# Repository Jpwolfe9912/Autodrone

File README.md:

# F722 Flight Controller V4

[Autodrone.pdf](https://github.com/Jpwolfe9912/Autodrone/files/7485937/Autodrone.pdf)

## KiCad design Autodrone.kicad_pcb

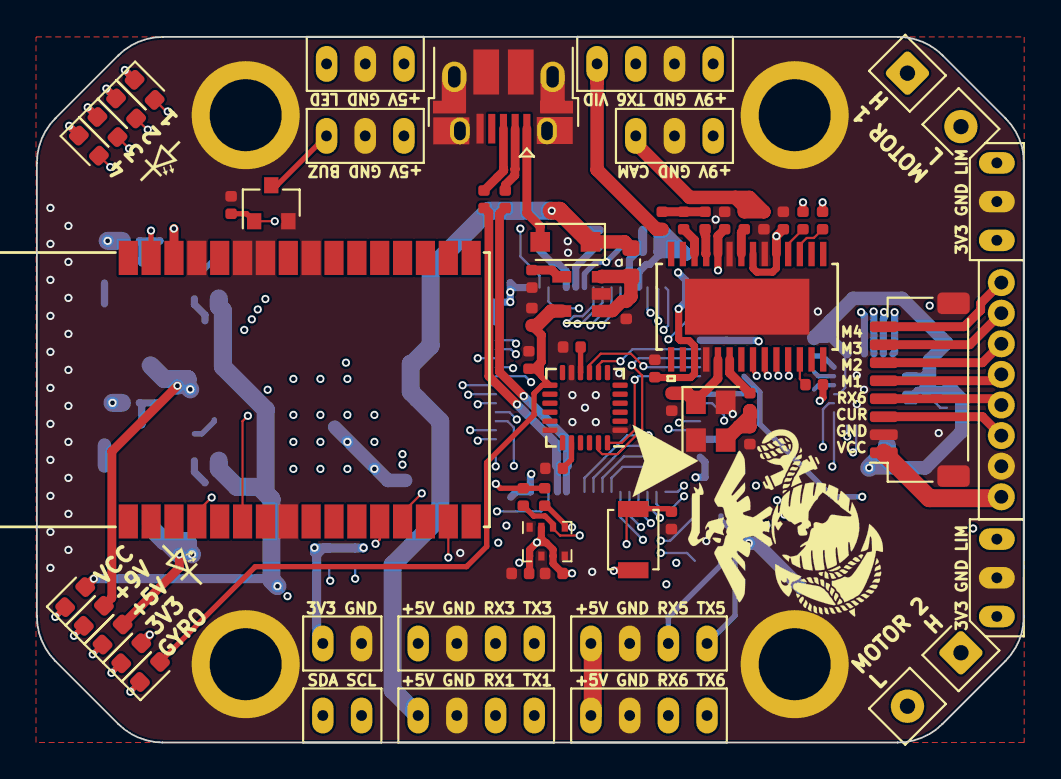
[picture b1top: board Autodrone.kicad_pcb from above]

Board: 6 copper layers, 54.8 x 39.2 mm, 142 parts (0 on the bottom side), 111 nets.

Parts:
C1, C2, C6, C8, C18, C20, C21, C22, C31, C32, C33, C34, C40, C41, C42, C43, C44, C45: 0.1uF; C_0402_1005Metric
C3: 33uF; C_0402_1005Metric
C4: 22uF; C_0402_1005Metric
C5, C7, C39: 4.7uF; C_0402_1005Metric
C9, C10: 330pF; C_0402_1005Metric
C11, C12: 1pF; C_0402_1005Metric
C13, C14, C29, C30: 10uF; C_0402_1005Metric
C15, C37: 1uF; C_0402_1005Metric
C16, C38: 10nF; C_0402_1005Metric
C17, C46: 2.2uF; C_0402_1005Metric
C19: 2.2nF; C_0402_1005Metric
C23, C25: 0.01uF; C_0402_1005Metric
C24: 100uF; CP_EIA-3528-15_AVX-H_Pad1.50x2.35mm_HandSolder
C26: 0.022uF; C_0402_1005Metric
C27: 0.47uF; C_0402_1005Metric
C28: 0.22uF; C_0402_1005Metric
C35, C36: 10pF; C_0402_1005Metric
D1, D2: 90V, 2A; D_SOD-123F
D3, D4: D_Schottky; D_SOD-123F
D5, D6: BLUE; LED_0603_1608Metric
D7, D8: RED; LED_0603_1608Metric
D9, D10: YELLOW; LED_0603_1608Metric
D11, D12: GREEN; LED_0603_1608Metric
D13: PURPLE; LED_0603_1608Metric
FB1, FB2: 100 @ 100 Mhz; L_0603_1608Metric
FB3: 100 @ 100 MHz; L_0603_1608Metric
H1, H2, H3, H4: MountingHole_Pad; MountingHole_2.7mm_Pad
J1, J2, J7, J8, J9: Conn_01x04; SolderWire-0.1sqmm_1x04_P3.6mm_D0.4mm_OD1mm
J3, J12, J13, J15, J17: Conn_01x03; SolderWire-0.1sqmm_1x03_P3.6mm_D0.4mm_OD1mm
J4: USB_B_Micro; USB_Micro-B_Amphenol_10103594-0001LF_Horizontal
J5: Conn_01x08; JST_SH_SM08B-SRSS-TB_1x08-1MP_P1.00mm_Horizontal
J6: Conn_01x08; SolderWire-0.1sqmm_1x08_D0.4mm_OD1mm
J10, J16: Conn_01x02; SolderWire-0.1sqmm_1x02_P3.6mm_D0.4mm_OD1mm
J11, J14: Conn_01x02; SolderWire-0.25sqmm_1x02_P4.2mm_D0.65mm_OD1.7mm
JP1, JP2: SolderJumper_2_Open; SolderJumper-2_P1.3mm_Open_TrianglePad1.0x1.5mm
L1: EGA
L2: Arrow
L3: 6.8uH; L_Bourns-SRN3015
L4: 8.2uH; L_Bourns-SRN3015
L5, L6: LED
Q1: BSS138; SOT-23
R1, R2: 20k; R_0402_1005Metric
R3: 3.8k; R_0402_1005Metric
R4: 2k; R_0402_1005Metric
R5, R6: 200k; R_0402_1005Metric
R7: 127k; R_0402_1005Metric
R8: 147k; R_0402_1005Metric
R9, R10, R23, R24: 2k2; R_0402_1005Metric
R11: 67k; R_0402_1005Metric
R12: 75k; R_0402_1005Metric
R13, R20, R22, R26: 10k; R_0402_1005Metric
R14, R15, R16, R21, R27, R28, R31, R32, R33, R34, R35, R36, R37: 1k; R_0402_1005Metric
R17, R18: 75; R_0402_1005Metric
R19: 589; R_0402_1005Metric
R25: 330; R_0402_1005Metric
R29, R30: 22; R_0402_1005Metric
SW1: SW_Push; SW_SPST_B3U-1000P
U1, U2: MP4462; DFN-10-1EP_3x3mm_P0.5mm_EP1.7x2.5mm
U3: LD1086DT33TR; TO-252-2
U4: LP2985-3.3; SOT-23-5
U5: MPU-6000; InvenSense_QFN-24_4x4mm_P0.5mm
U6: BMP280; Bosch_LGA-8_2x2.5mm_P0.65mm_ClockwisePinNumbering
U7: DRV8424E; VQFN-24-1EP_4x4mm_P0.5mm_EP2.45x2.45mm
U8: STLINK-V3MODS; STLINKV3MODS
U9: MAX7456EUI+; MAX7456EUI&plus_T
U10: STM32F722RETx; LQFP-64_10x10mm_P0.5mm
Y1: 27MHz; Oscillator_SMD_Abracon_ASE-4Pin_3.2x2.5mm
Y2: CSTNE8M00G55Z000R0; OSC_CSTNE8M00G55Z000R0

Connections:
+3.3VA: C37.1, C38.1, FB3.1, U10.13
+3V3: C14.1, C21.1, C22.1, C32.1, C33.1, C34.1, C39.1, C40.1, C41.1, C42.1, C43.1, C44.1, D8.2, FB3.2, J10.1, J13.1, J17.1, R9.2, R10.2, R14.1, R15.1, R16.1, R23.1, R24.1, SW1.1, U3.2, U6.2, U6.6, U6.8, U8.30, U9.3, U9.19, U9.21, U9.24, U10.1, U10.19, U10.32, U10.48, U10.64
+3V3_GYRO: C17.1, C18.1, D6.2, U4.5, U5.13
+4V5: D3.1, D4.1, FB1.2, FB2.2, J1.1
+5V: C3.1, C23.1, C24.1, C25.1, C27.1, C28.2, D3.2, D10.2, J2.1, J7.1, J8.1, J12.1, J15.1, L3.2, R1.1, R11.1, R13.2, U7.1, U7.8, U7.10, U7.21
+5V_USB: D4.2, J4.1
+9V: C4.1, D12.2, J3.1, J9.1, L4.2, R2.1
/Barometer/I2C1_SCL: R9.1, U6.4, U10.61
/Barometer/I2C1_SDA: R10.1, U6.3, U10.62
/CAM: C31.1, J3.3, R18.2
/Connectors/BUZ: J12.3, Q1.3
/Connectors/CURR_SENSE: J5.3, J6.3, U10.26
/Connectors/I2C2_SCL: J16.2, R24.2, U10.28
/Connectors/I2C2_SDA: J16.1, R23.2, U10.29
/Connectors/LED_STRIP: J15.3, U10.57
/Connectors/LIMIT1_INT: J13.3, U10.2
/Connectors/LIMIT2_INT: J17.3, U10.3
/Connectors/M1: J5.5, J6.5, U10.17
/Connectors/M2: J5.6, J6.6, U10.16
/Connectors/M3: J5.7, J6.7, U10.15
/Connectors/M4: J5.8, J6.8, U10.14
/Connectors/UART5_RX_CONN: J2.3, JP1.2
/Connectors/UART5_TX_CONN: J2.4, JP2.2
/Connectors/USART1_RX: J1.3, U10.59
/Connectors/USART1_TX: J1.4, U10.58
/Connectors/USART3_RX: J8.3, U10.52
/Connectors/USART3_TX: J8.4, U10.51
/Connectors/USART6_RX: J5.4, J6.4, J7.3, U10.38
/Connectors/USART6_TX: J7.4, J9.3, U10.37
/Connectors/USB_D+: J4.3, R30.1
/Connectors/USB_D-: J4.2, R29.1
/Debugger/NRST: C45.1, U8.31, U10.7
/Debugger/SWCLK: U8.13, U10.49
/Debugger/SWDIO: U8.4, U10.46
/Debugger/SWO: U8.6, U10.55
/Gyro/CPOUT: C19.1, U5.20
/Gyro/REGOUT: C20.1, U5.10
/Gyro/SPI1_CS: U5.8, U10.20
/Gyro/SPI1_MISO: U5.9, U10.22
/Gyro/SPI1_MOSI: U5.24, U10.23
/Gyro/SPI1_SCK: U5.23, U10.21
/MCU/3V3: D8.1, R32.1
/MCU/3V3_GYRO: D6.1, R28.1
/MCU/5V: D10.1, R34.1
/MCU/9V: D12.1, R36.1
/MCU/+VCC: D13.1, R37.1
/MCU/BLUE: D5.1, R27.1
/MCU/BOOT0: R22.1, SW1.2, U10.60
/MCU/BUZ_MCU: Q1.1, R26.1, U10.56
/MCU/D+: R29.2, U10.44
/MCU/D-: R30.2, U10.45
/MCU/GREEN: D11.1, R35.1
/MCU/HSE_IN: U10.5, Y2.1
/MCU/HSE_OUT: R25.1, U10.6
/MCU/LED_1: D5.2, U10.8
/MCU/LED_2: D7.2, U10.9
/MCU/LED_3: D9.2, U10.10
/MCU/LED_4: D11.2, U10.11
/MCU/RED: D7.1, R31.1
/MCU/SPI2_CS: U9.8, U10.33
/MCU/SPI2_MISO: U9.11, U10.35
/MCU/SPI2_MOSI: U9.9, U10.36
/MCU/SPI2_SCK: U9.10, U10.34
/MCU/UART5_RX: JP1.1, U8.15, U10.54
/MCU/UART5_TX: JP2.1, U8.12, U10.53
/MCU/VCAP: C46.1, U10.30
/MCU/VCC_SENSE: R20.2, R21.2, U10.25
/MCU/WORM1_DIR: U7.19, U10.39
/MCU/WORM1_PWM: U7.20, U10.41
/MCU/WORM2_DIR: U7.17, U10.40
/MCU/WORM2_PWM: U7.18, U10.42
/MCU/YELLOW: D9.1, R33.1
/OSD/CLKIN: C35.2, U9.5, Y1.1
/OSD/HSYNC: R14.2, U9.18
/OSD/LOS: R16.2, U9.12
/OSD/LSYNC: R15.2, U9.17
/OSD/SAG: C30.2, U9.25
/OSD/VIN: C31.2, U9.22
/OSD/VOUT: C29.2, U9.26
/OSD/XFB: R19.1, U9.6
/Power/BP_1V8: C16.1, U4.4
/Power/BS_5: C1.1, U1.10
/Power/BS_9: C2.1, U2.10
/Power/COMP_5: C10.1, C12.1, U1.4
/Power/COMP_9: C9.1, C11.1, U2.4
/Power/FB_5: R1.2, R3.1, U1.5
/Power/FB_9: R2.2, R4.1, U2.5
/Power/FREQ_5: R5.1, U1.7
/Power/FREQ_9: R6.1, U2.7
/Power/SW_5: C1.2, D1.1, L3.1, U1.1, U1.2
/Power/SW_9: C2.2, D2.1, L4.1, U2.1, U2.2
/Power/VIN_1V8: C15.1, FB2.1, U4.1, U4.3
/Power/VIN_3V3: C13.1, FB1.1, U3.3
/VID: J9.4, R17.1
/WORM1_H: J11.1, U7.3
/WORM1_L: J11.2, U7.4
/WORM2_H: J14.1, U7.6
/WORM2_L: J14.2, U7.5
/WormDriver/CPH: C26.2, U7.23
/WormDriver/CPL: C26.1, U7.22
/WormDriver/VCP: C28.1, U7.24
/WormDriver/VREF: R11.2, R12.2, U7.12, U7.13
/WormDriver/nFAULT: R13.1, U7.11
GND: C3.2, C4.2, C5.1, C6.1, C7.1, C8.1, C11.2, C12.2, C13.2, C14.2, C15.2, C16.2, C17.2, C18.2, C19.2, C20.2, C21.2, C22.2, C23.2, C24.2, C25.2, C27.2, C32.2, C33.2, C34.2, C35.1, C36.1, C39.2, C40.2, C41.2, C42.2, C43.2, C44.2, C45.2, C46.2, D1.2, D2.2, H1.1, H2.1, H3.1, H4.1, J1.2, J2.2, J3.2, J4.5, J4.6, J5.2, J6.2, J7.2, J8.2, J9.2, J10.2, J12.2, J13.2, J15.2, J17.2, Q1.2, R3.2, R4.2, R5.2, R6.2, R7.2, R8.2, R12.1, R18.1, R21.1, R22.2, R26.2, R27.2, R28.2, R31.2, R32.2, R33.2, R34.2, R35.2, R36.2, R37.2, U1.6, U2.6, U3.1, U4.2, U5.1, U5.11, U5.18, U6.1, U6.5, U6.7, U7.2, U7.7, U7.9, U7.14, U7.15, U7.16, U7.25, U8.8, U8.24, U8.26, U8.27, U8.29, U9.4, U9.20, U9.23, U9.29, U10.18, U10.31, U10.47, U10.63, Y1.2, Y1.4, Y2.2
GNDA: C37.2, C38.2, U10.12
unnamed: C9.2, R8.1
unnamed: C10.2, R7.1
unnamed: C29.1, C30.1, R17.2
unnamed: C36.2, R19.2, Y1.3
unnamed: R25.2, Y2.3
VCC: C5.2, C6.2, C7.2, C8.2, D13.2, J5.1, J6.1, R20.1, U1.8, U1.9, U2.8, U2.9

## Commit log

2021-10-15 New files
2021-11-02 Lots of changes made
2021-11-03 Cosmetic changes to schematic
2021-11-04 Finished routing
2021-11-12 Increased board size and added silkscreen text
2021-11-14 Added reference for 100uF cap
2021-11-14 Updated schematic PDF
2021-11-14 Changed color of labels
2021-11-24 Changes made
